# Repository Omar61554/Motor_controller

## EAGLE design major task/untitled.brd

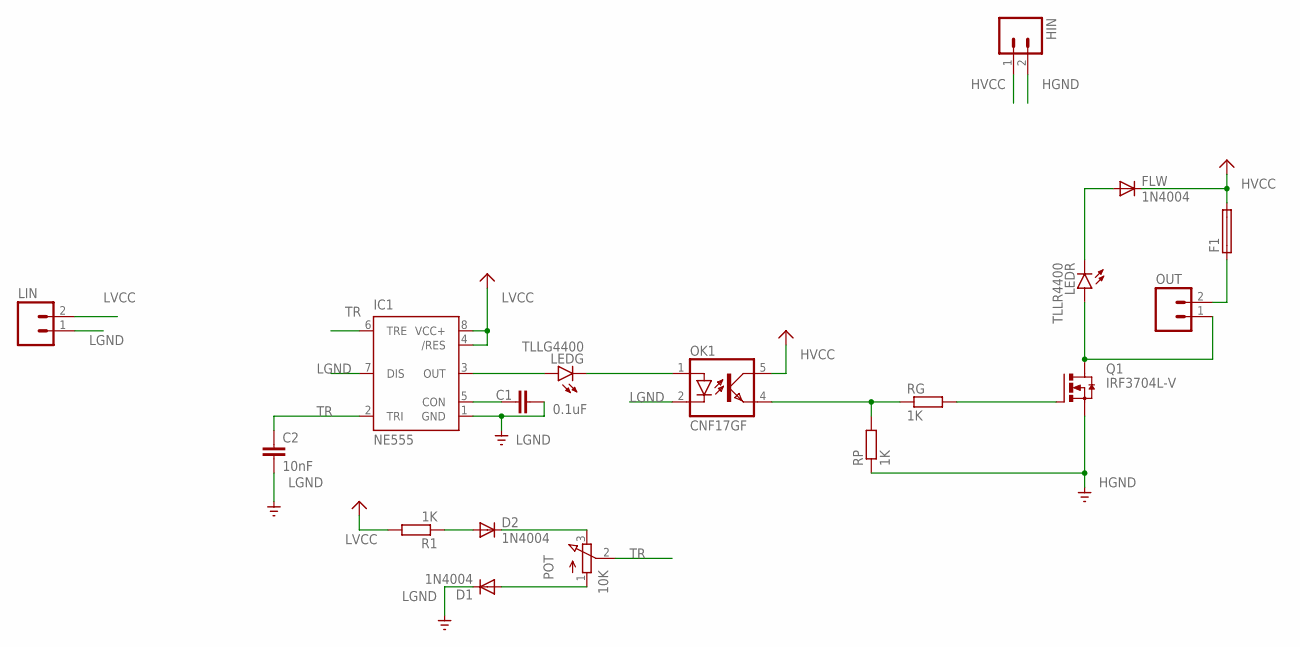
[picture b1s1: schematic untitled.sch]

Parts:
C1: 0.1uF; C2.5-3
C2: 10nF; C2.5-3
D1, D2: 1N4004; DO41-10
F1: 19559
FLW: 1N4004; DO41-10
HIN: M02; 02P
IC1: NE555; DIL-08
LEDG: TLLG4400; LED3MM
LEDR: TLLR4400; LED3MM
LIN: M02; 02P
OK1: CNF17GF; DIL06B
OUT: M02; 02P
POT: 10K; 3RP/1610N
Q1: IRF3704L-V; TO262-V
R1: 1K; 0204/7
RG: 1K; 0204/7
RP: 1K; 0204/7

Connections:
HGND: HIN.2, Q1.3 (S), RP.1
HVCC: F1.2, FLW.C, HIN.1, OK1.5 (COL)
LGND: C1.1, C2.2, D1.C, IC1.1 (GND), IC1.7 (DIS), LIN.1, OK1.2 (C)
LVCC: IC1.4 (/RES), IC1.8 (VCC+), LIN.2, R1.2
unnamed: IC1.3 (OUT), LEDG.A
unnamed: LEDG.K (C), OK1.1 (A)
unnamed: C1.2, IC1.5 (CON)
unnamed: D2.C, POT.3 (E)
unnamed: D1.A, POT.1 (A)
unnamed: D2.A, R1.1
unnamed: OK1.4 (EMIT), RG.1, RP.2
unnamed: Q1.1 (G), RG.2
unnamed: LEDR.A, OUT.1, Q1.2 (D)
unnamed: FLW.A, LEDR.K (C)
unnamed: F1.1, OUT.2
TR: C2.1, IC1.2 (TRI), IC1.6 (TRE), POT.2 (S)

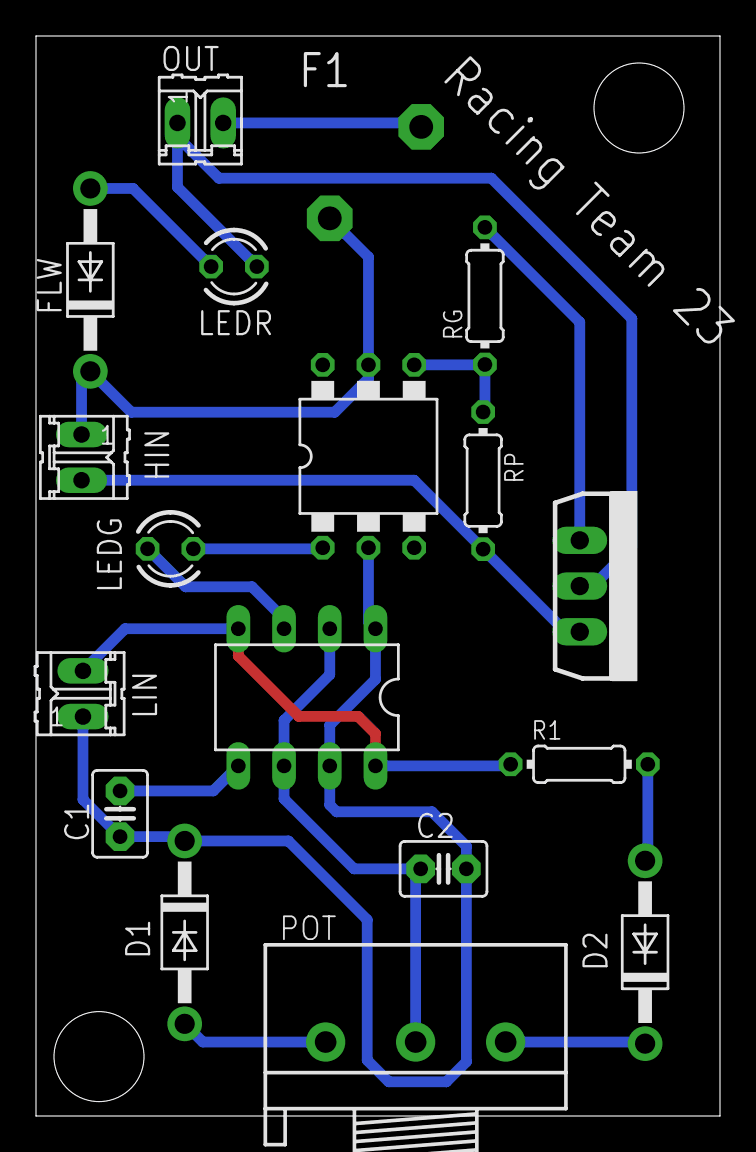
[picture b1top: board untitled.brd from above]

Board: 2 copper layers, 38.0 x 60.0 mm, 18 parts (1 on the bottom side), 16 nets.

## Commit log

2023-11-20 Eagle
2023-11-23 TRACES
